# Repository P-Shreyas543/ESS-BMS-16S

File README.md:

# ESS-BMS-16S — Open 16S LFP Battery Management System for Energy Storage

A compact, open-hardware battery management system for 16S LFP (51.2 V) energy-storage packs — home storage, server-rack batteries, telecom backup — designed in KiCad 10 for JLCPCB fabrication and assembly.

The goal is a BMS that matches the features of the widely used Chinese ESS boards (Daly, JBD, JK, Seplos, PACE) and goes beyond them where they are weak: protection that does not depend on firmware, measured switch and pre-charge health, deeper diagnostics, and open, documented protocols.

> **Status (2026-11-25): schematic v1.2 done — PCB layout next. Not built, not tested, not production ready.**
> v1.2 installs a hybrid control-board power tree: restores the v1.0 `+5V` LM5013 non-synchronous buck with the commercial `LM5013DDAR` and v1.0 power latch, and keeps the v1.1 transformer-isolated (2.5 kVAC) `+5V_ISO` chain with the AEC-Q100 `SN6505B-Q1` ([what changed](docs/SCHEMATIC_V1.md#10-revision-v12-2026-11-25)).
> The schematic is complete for both boards of the stack (control board + power board), verified against its pin-level spec and independently reviewed: [`docs/SCHEMATIC_V1.md`](docs/SCHEMATIC_V1.md), PDFs [control board](docs/schematic/control_board_v1.pdf) / [power board](docs/schematic/power_board_v1.pdf). Do not order boards from this repository yet: several bring-up gates (including an LM5013 EMC pre-scan) and owner decisions are open. See [Project status](#project-status).

---

## Target specification (v1)

| Item | Target |
|---|---|
| Cells | 16S LFP, 40.0–58.4 V pack |
| Current | 200 A continuous, on-board back-to-back high-side N-MOSFET switch |
| Current sense | on-board 100 µΩ shunt, BQ76952 coulomb counter + independent fast trip |
| Cell monitor | TI BQ76952 (16 cells, hardware protections, high-side FET drivers, pre-charge) |
| Balancing | external passive ~105 mA per cell + header for an optional 1–2 A active balancer, charge-based balancing firmware |
| Temperature | pack NTCs + FET-bank and shunt sensors |
| MCU | STM32G473RCT6 (3× FDCAN, 256 KB flash) |
| Communications | 2× isolated CAN, 2× isolated RS-485 (inverter + parallel-pack link, RJ45 ×4), ESP32-C3 Bluetooth / Wi-Fi |
| Safety | MCU-independent hardware gate-kill (AFE faults + latched over-current), dual watchdog, switch / pre-charge fault checks |
| Other | sleep / ship mode with wake button, SOC LEDs, 2 dry contacts, heater output, RTC-stamped fault log (FRAM + flash), field firmware update |

The numbers above are design targets; the verified values are kept in [`PROJECT.md`](PROJECT.md) and the architecture documents as they are confirmed.

## How it compares

A feature benchmark of current Daly, JBD, JK, Seplos, PACE and ANT products is in [`docs/research/02_competitors.md`](docs/research/02_competitors.md). In short: every serious product has sleep mode, an app, parallel packs, dry contacts and inverter protocols — this design adds those, plus features none of them documents (independent hardware trip, switch health checks, busbar / cell resistance diagnostics, open protocols, timestamped deep logging).

## Project status

| Step | State |
|---|---|
| Requirements and original runbook | done ([`instructions.md`](instructions.md)) |
| Schematic redraw to house style (6 sheets, connectivity proven unchanged) | done 2026-11-17 |
| Electrical / requirements review | done — findings in [`docs/research/`](docs/research/) and [`AGENT_TASKS.md`](AGENT_TASKS.md) |
| Feature and component research (AFE, competitors, balancing, power path, MCU) | done — [`docs/research/00_SUMMARY.md`](docs/research/00_SUMMARY.md) |
| Architecture v1 (power tree, power stage, AFE, MCU pin map, sheet plan) | done — [`docs/ARCHITECTURE.md`](docs/ARCHITECTURE.md) (updated for schematic v1) |
| Part selection with live LCSC verification | done — [`docs/BOM_v1.md`](docs/BOM_v1.md) |
| Schematic v1 / v1.2: two KiCad projects, 10 sheets, 784 references (v1.2); pin-level spec → independent review → scripted drawing → netlist-vs-spec match on all 10 sheets, ERC 0 errors on both boards → final independent review (0 blockers) + v1-vs-v1.1 comparison | v1 done 2026-11-24, v1.1 2026-11-25 (`ca3a7a3` fallback), v1.2 hybrid power tree 2026-11-25 — [`docs/SCHEMATIC_V1.md`](docs/SCHEMATIC_V1.md), [design notes](docs/design/), [reviews](docs/reviews/), [BOM CSV](docs/bom/bom_schematic_v1.csv) |
| PCB layout, DRC, fabrication outputs | **next** |
| Bring-up and bench tests (incl. the short-circuit test) | planned |

## System block diagram

*Interactive full-resolution diagram: [`docs/block_diagram.svg`](docs/block_diagram.svg) (power path, power board hardware safety island, B2B stack interface, control board v1.2 hybrid power tree, comms, IO, pending owner decisions, and planned additions).*

## Repository layout

| Path | Content |
|---|---|
| `Automotive_ESS_BMS.kicad_pro` / `.kicad_sch` | control-board KiCad project and root schematic (with block diagram) |
| `01_*`, `02_*`, `03_*`, `05_*`, `06_*`, `08_*`, `09_*`, `10_*.kicad_sch` | control-board sheets: power supply, AFE / cell monitor, MCU, aux outputs, communications, IO / front panel, wireless, memory / sensors |
| `power_board/` | power-board KiCad project: `04_Current_Sensing`, `07_Power_Stage` |
| `docs/SCHEMATIC_V1.md`, `docs/schematic/` | schematic v1 overview (board split, B2B pin map, verification, bring-up gates, firmware rules, open decisions) and PDFs of both boards |
| `docs/design/`, `docs/reviews/` | per-sheet design notes (calculations, decisions, LCSC verification) and the spec / schematic reviews |
| `docs/ARCHITECTURE.md`, `docs/architecture/`, `docs/BOM_v1.md`, `docs/bom/` | system architecture and part selection |
| `symbols/`, `footprints.pretty/`, `3d_models/` | project-local libraries (`${KIPRJMOD}` paths, portable) |
| `PROJECT.md` | project facts, nets, domains, parts and the owner **decisions log** |
| `DESIGN_NOTES.md` | calculations and design reasoning, per sheet |
| `docs/research/` | research reports with datasheet / source citations |
| `docs/plans/` | the original 2026-10 subsystem plans (historical background; the decisions log in `PROJECT.md` wins) |
| `LICENSE`, `tools/LICENSE` | CERN-OHL-S-2.0 (hardware), MIT (tools) |
| `instruction.md` | the engineering playbook this project follows (workflow, style, verification) |
| `instructions.md` | original product requirements |
| `AGENT_TASKS.md` | task queue and verification reports of each work step |
| `tools/` | Python helpers: environment check, lossless KiCad s-expression edit, netlist compare, ERC summary, render |

## Engineering method

Every change follows [`instruction.md`](instruction.md):

* **Connectivity proof:** each redraw is verified with a netlist comparison (`tools/schematic/netcmp.py`) — the net list must be identical unless a change was decided.
* **ERC** on the root sheet after every step, with the result recorded.
* **Visual check** of every sheet and block from rendered images.
* **Part data** verified on the distributor page (LCSC number, MPN, stock) — never from memory.
* **Decisions** recorded with date in `PROJECT.md`; calculations in `DESIGN_NOTES.md` with datasheet page references (`DS p.x`), own calculations (`calc`) and estimates (`est.`) marked.

## Opening the project

1. Install KiCad 10.
2. Open `Automotive_ESS_BMS.kicad_pro`. The project libraries resolve through `${KIPRJMOD}`; no global library setup is needed.
3. Optional: `python tools/check_env.py .` checks the toolchain (KiCad CLI, Python packages, renderer).

## Standards referenced

IPC-2221B (clearance), IPC-7351B (land patterns), IPC-A-610 Class 3, IEC 60664-1, IEC 62619 / UL 1973 (stationary storage), UL 9540A, ISO 26262 principles, AEC-Q100/101/200 where available. Certification is not claimed.

## Third-party material

* **Datasheets and app notes are not included.** They are copyrighted by their manufacturers. The design notes and research reports cite them by document number and page; download them from the manufacturer (TI, ST, Vishay, …) or the LCSC product page.
* **3D models are not included** (vendor licences vary). Footprints reference them under `${KIPRJMOD}/3d_models/`; fetch them from the manufacturer or with `easyeda2kicad` for local use.
* Product and company names (Daly, JBD, JK, Seplos, PACE, ANT, Pylontech, Victron, …) are trademarks of their owners and are used only to identify products in the comparison. Competitor data is taken from public documents and listings, cited in `docs/research/02_competitors.md`; no affiliation or endorsement is implied.

## Disclaimer

This is a **work-in-progress design shared for learning and review, not a certified product.** Lithium battery packs store large amounts of energy; a fault in a BMS can cause fire, explosion, electric shock or injury. Anyone who builds, modifies or uses this design does so at their own risk and is responsible for testing it and for meeting the safety standards that apply where it is used (for example IEC 62619, UL 1973, UL 9540A). The design is provided **"as is", without any warranty**, as stated in section 6 (Disclaimer and Liability) of the CERN-OHL-S-2.0 licence. No certification or compliance is claimed.

## License

* **Hardware** (schematics, PCB, libraries, design documentation): [CERN Open Hardware Licence v2 — Strongly Reciprocal](LICENSE) (`CERN-OHL-S-2.0`). You may use, modify, make and sell it; if you distribute a modified design or products made from it, you must publish your modified source under the same licence.
* **Software tools** in `tools/`: [MIT](tools/LICENSE).

Copyright © 2026 Shreyas P. Source location: this repository.

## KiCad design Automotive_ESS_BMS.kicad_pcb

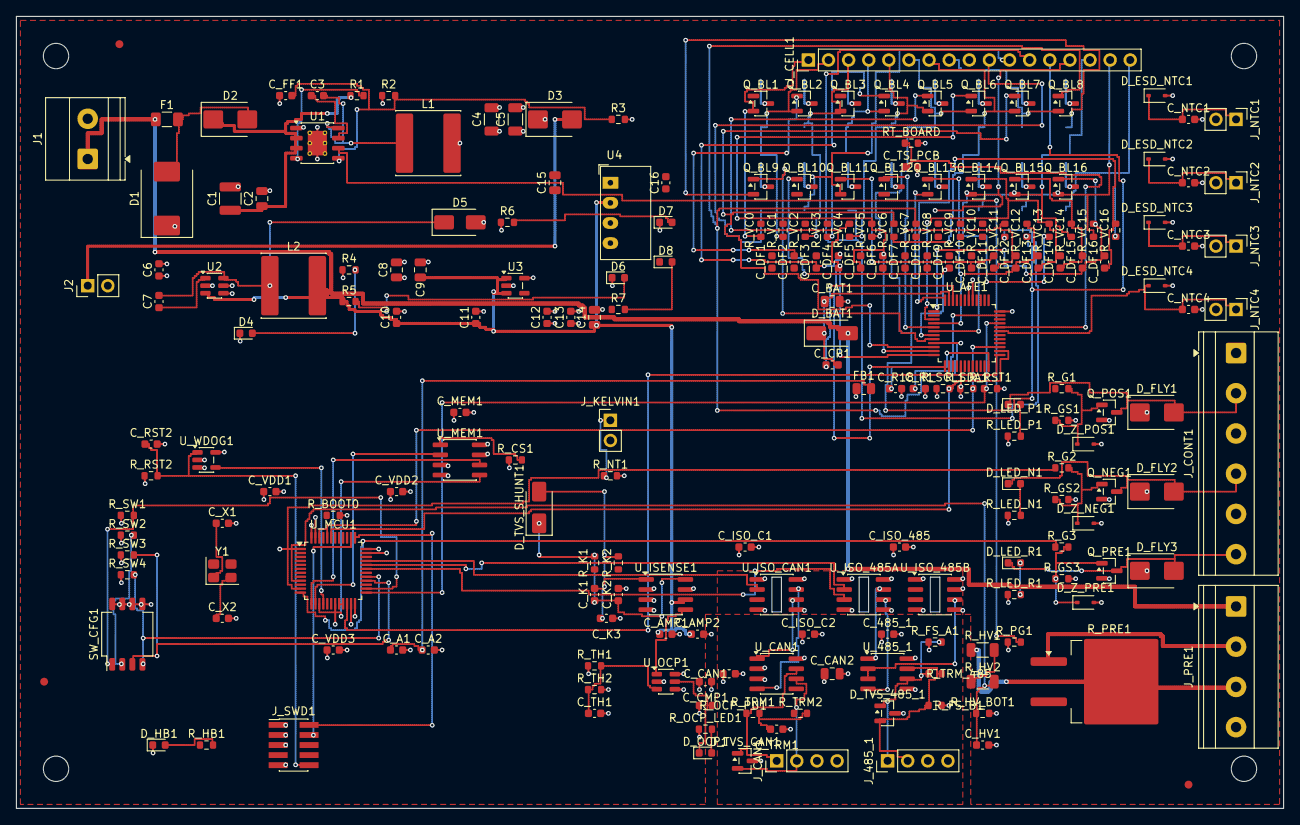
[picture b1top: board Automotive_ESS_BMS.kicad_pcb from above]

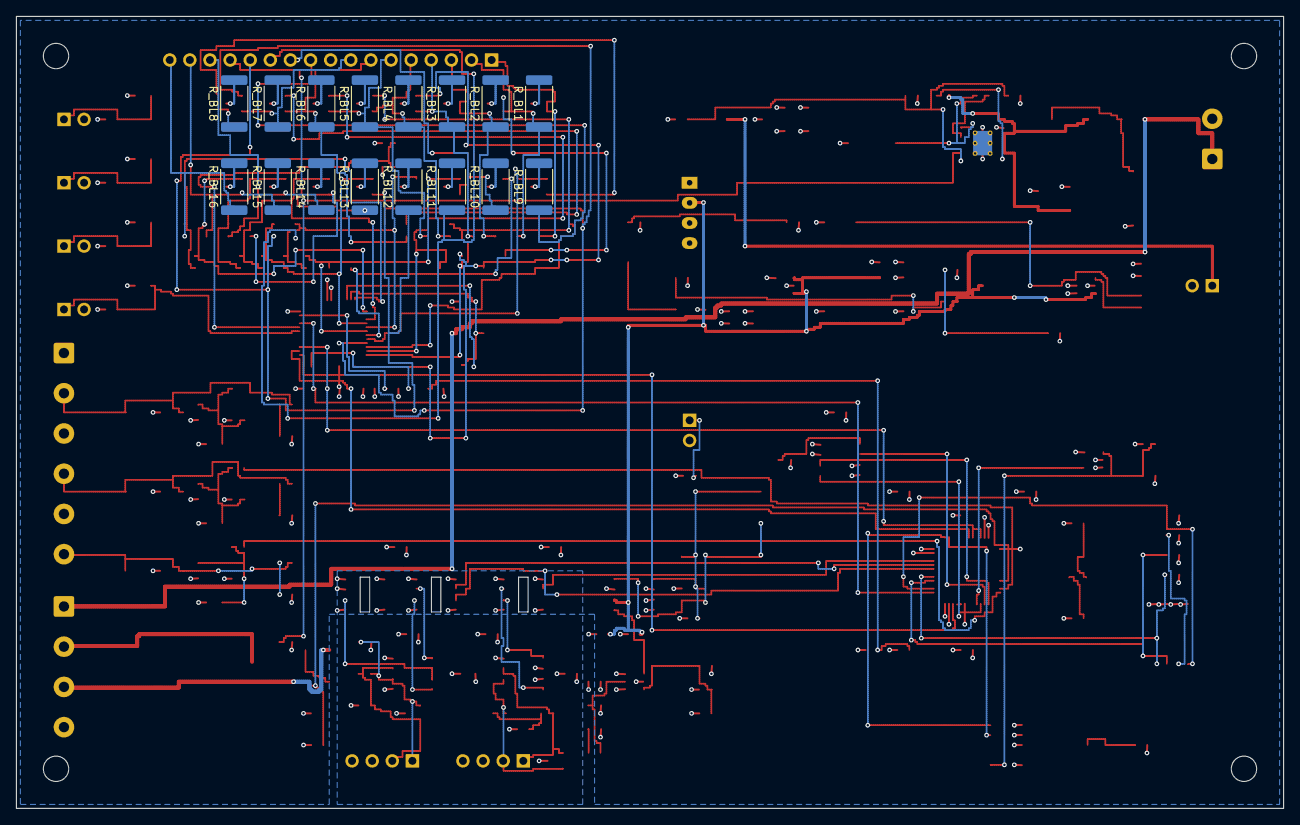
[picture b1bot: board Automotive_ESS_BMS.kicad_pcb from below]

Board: 4 copper layers, 160.0 x 100.0 mm, 231 parts (16 on the bottom side), 141 nets.

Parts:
C1: 10uF 100V; C_1210_3225Metric
C2: 100nF 100V; C_0805_2012Metric
C3, C6, C16: 100nF 50V; C_0603_1608Metric
C4: 22uF 25V; C_1206_3216Metric
C5: 10uF 25V; C_1206_3216Metric
C7: 100nF 25V; C_0603_1608Metric
C8: 10uF 25V; C_0805_2012Metric
C9: 22uF 10V; C_0805_2012Metric
C10, C13: 100nF 16V; C_0603_1608Metric
C11: 1uF 16V; C_0603_1608Metric
C12: 4.7uF 10V; C_0603_1608Metric
C14: 4.7uF 16V; C_0805_2012Metric
C15: 10uF 16V; C_0805_2012Metric
C_485_1: 100nF 16V; C_0603_1608Metric
C_A1: 1uF 16V; C_0603_1608Metric
C_A2: 100nF 16V; C_0603_1608Metric
C_AMP1: 1uF 16V; C_0603_1608Metric
C_AMP2: 100nF 16V; C_0603_1608Metric
C_BAT1: 1uF 100V; C_0805_2012Metric
C_CAN1: 100nF 16V; C_0603_1608Metric
C_CAN2: 4.7uF 16V; C_0805_2012Metric
C_CMP1: 100nF 16V; C_0603_1608Metric
C_CP1: 100nF 50V; C_0603_1608Metric
C_DF1, C_DF2, C_DF3, C_DF4, C_DF5, C_DF6, C_DF7, C_DF8, C_DF9, C_DF10, C_DF11, C_DF12, C_DF13, C_DF14, C_DF15, C_DF16: 100nF 50V; C_0603_1608Metric
C_FF1: 47pF 50V; C_0603_1608Metric
C_HV1: 10nF 50V; C_0603_1608Metric
C_ISO_485: 100nF 16V; C_0603_1608Metric
C_ISO_C1, C_ISO_C2: 100nF 16V; C_0603_1608Metric
C_K1: 100nF 50V; C_0603_1608Metric
C_K2, C_K3: 10nF 50V; C_0603_1608Metric
C_MEM1: 100nF 16V; C_0603_1608Metric
C_NTC1, C_NTC2, C_NTC3, C_NTC4: 10nF 50V; C_0603_1608Metric
C_R1, C_R18: 2.2uF 10V; C_0603_1608Metric
C_RST2: 100nF 16V; C_0603_1608Metric
C_TH1: 10nF 50V; C_0603_1608Metric
C_TRM1: 4.7nF 50V; C_0603_1608Metric
C_TS_PCB: 10nF 50V; C_0603_1608Metric
C_VDD1, C_VDD2, C_VDD3: 100nF 16V; C_0603_1608Metric
C_X1, C_X2: 18pF 50V; C_0603_1608Metric
D1: SMCJ75A; D_SMC
D2: SS310 (100V 3A); D_SMB
D3: SS34 (40V 3A); D_SMB
D4: Blue 12V; LED_0603_1608Metric
D5: SS14; D_SMA
D6: Yellow 5V; LED_0603_1608Metric
D7: Green 3V3; LED_0603_1608Metric
D8: Orange 5V_ISO; LED_0603_1608Metric
D_BAT1: SS110 (100V 1A); D_SMA
D_ESD_NTC1, D_ESD_NTC2, D_ESD_NTC3, D_ESD_NTC4: ESD5V0D3B; D_SOD-323
D_FLY1, D_FLY2, D_FLY3: SS34 (40V 3A); D_SMB
D_HB1: Blue Heartbeat; LED_0603_1608Metric
D_LED_N1: Green Cont- ON; LED_0603_1608Metric
D_LED_P1: Green Cont+ ON; LED_0603_1608Metric
D_LED_R1: Amber Precharge ON; LED_0603_1608Metric
D_OCP1: Red OCP Trip; LED_0603_1608Metric
D_TVS_485_1: SM712; SOT-23
D_TVS_CAN1: NUP2105LT1G; SOT-23
D_TVS_SHUNT1: SMAJ5.0CA; D_SMA
D_Z_NEG1: BZX84-C18 (18V Clamp); D_SOD-323
D_Z_POS1: BZX84-C18 (18V Clamp); D_SOD-323
D_Z_PRE1: BZX84-C18 (18V Clamp); D_SOD-323
F1: 2.5A 125V; Fuse_1206_3216Metric
FB1: 600R @ 100MHz; R_0805_2012Metric
FID1, FID2, FID3: Fiducial_1mm_Mask2mm
J1: Pack Input (16V-72V); TerminalBlock_Phoenix_MKDS-1,5-2-5.08_1x02_P5.08mm_Horizont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
J2: Aux Bench 12V; PinHeader_1x02_P2.54mm_Vertical
J_485_1: Isolated RS-485 Modbus; PinHeader_1x04_P2.54mm_Vertical
J_CAN1: Isolated CAN-FD Bus; PinHeader_1x04_P2.54mm_Vertical
J_CELL1: 16S Cell Sense Tap; PinHeader_1x17_P2.54mm_Vertical
J_CONT1: Contactor Coils (12V); TerminalBlock_Phoenix_MKDS-1,5-6-5.08_1x06_P5.08mm_Horizont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
J_KELVIN1: Ext Shunt Kelvin Sense; PinHeader_1x02_P2.54mm_Vertical
J_NTC1: NTC Temp Sens 1; PinHeader_1x02_P2.54mm_Vertical
J_NTC2: NTC Temp Sens 2; PinHeader_1x02_P2.54mm_Vertical
J_NTC3: NTC Temp Sens 3; PinHeader_1x02_P2.54mm_Vertical
J_NTC4: NTC Temp Sens 4; PinHeader_1x02_P2.54mm_Vertical
J_PRE1: Inverter DC Bus Precharge; TerminalBlock_Phoenix_MKDS-1,5-4-5.08_1x04_P5.08mm_Horizont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
J_SWD1: Cortex SWD Debug; PinHeader_2x05_P1.27mm_Vertical_SMD
L1: 47uH 1.8A; L_Sunlord_SWPA8040S
L2: 10uH 1.5A; L_Sunlord_SWPA8040S
MH1, MH2, MH3, MH4: MountingHole_3.2mm_M3
Q_BL1, Q_BL2, Q_BL3, Q_BL4, Q_BL5, Q_BL6, Q_BL7, Q_BL8, Q_BL9, Q_BL10, Q_BL11, Q_BL12, Q_BL13, Q_BL14, Q_BL15, Q_BL16: AO3400A (30V 5A); SOT-23
Q_NEG1: SQ2318EY (40V 8A); SOT-23
Q_POS1: SQ2318EY (40V 8A); SOT-23
Q_PRE1: SQ2318EY (40V 8A); SOT-23
R1: 100k; R_0603_1608Metric
R2: 90.9k 1%; R_0603_1608Metric
R3: 10.0k 1%; R_0603_1608Metric
R4: 4.7k; R_0603_1608Metric
R5, R7: 1.5k; R_0603_1608Metric
R6: 1.0k; R_0603_1608Metric
RT_BOARD: NTC 10k 1% (PCB Temp); R_0603_1608Metric
R_BL1, R_BL2, R_BL3, R_BL4, R_BL5, R_BL6, R_BL7, R_BL8, R_BL9, R_BL10, R_BL11, R_BL12, R_BL13, R_BL14, R_BL15, R_BL16: 33R 1W 1%; R_2512_6332Metric
R_BOOT0: 10k; R_0603_1608Metric
R_CS1: 10k; R_0603_1608Metric
R_FS_A1: 560R 1%; R_0603_1608Metric
R_FS_B1: 560R 1%; R_0603_1608Metric
R_G1, R_G2, R_G3: 100R; R_0603_1608Metric
R_GS1, R_GS2, R_GS3: 47k; R_0603_1608Metric
R_HB1: 1.0k; R_0603_1608Metric
R_HV1, R_HV2: 1.00M 1% 200V; R_1206_3216Metric
R_HV_BOT1: 20.0k 0.1%; R_0603_1608Metric
R_K1, R_K2: 10.0R 1%; R_0603_1608Metric
R_LED_N1: 4.7k; R_0603_1608Metric
R_LED_P1: 4.7k; R_0603_1608Metric
R_LED_R1: 4.7k; R_0603_1608Metric
R_NT1: 0R (Kelvin Ground Tie); R_0603_1608Metric
R_OCP_LED1: 1.5k; R_0603_1608Metric
R_OCP_PU1: 10k; R_0603_1608Metric
R_PG1: 100k; R_0603_1608Metric
R_PRE1: 50R 25W 5%; TO-263-2
R_RST1, R_RST2: 10k; R_0603_1608Metric
R_SCL1: 4.7k; R_0603_1608Metric
R_SDA1: 4.7k; R_0603_1608Metric
R_SW1, R_SW2, R_SW3, R_SW4: 10k; R_0603_1608Metric
R_TH1: 4.7k 1%; R_0603_1608Metric
R_TH2: 100k 1%; R_0603_1608Metric
R_TRM1, R_TRM2: 60.4R 1%; R_0603_1608Metric
R_TRM_485: 120R 1%; R_0603_1608Metric
R_VC0, R_VC1, R_VC2, R_VC3, R_VC4, R_VC5, R_VC6, R_VC7, R_VC8, R_VC9, R_VC10, R_VC11, R_VC12, R_VC13, R_VC14, R_VC15, R_VC16: 1.00k 1%; R_0603_1608Metric
SW_CFG1: 7S-16S & Chem CFG; SW_DIP_SPSTx04_Slide_Copal_CHS-04B_W7.62mm_P1.27mm
U1: LM5164-Q1; HSOP-8-1EP_3.9x4.9mm_P1.27mm_EP2.41x3.1mm_ThermalVias
U2: LMR16006YQ5; SOT-23-6
U3: AP2112K-3.3; SOT-23-5
U4: B0505S-1WR3; Converter_DCDC_Murata_CRE1xxxxxxSC_THT
U_485_1: THVD1450DR; SOIC-8_3.9x4.9mm_P1.27mm
U_AFE1: BQ76952-Q1; TQFP-48_7x7mm_P0.5mm
U_CAN1: TJA1051T/3; SOIC-8_3.9x4.9mm_P1.27mm
U_ISENSE1: INA240A2-Q1; SOIC-8_3.9x4.9mm_P1.27mm
U_ISO_485A, U_ISO_485B: ISO7721-Q1; SOIC-8_3.9x4.9mm_P1.27mm
U_ISO_CAN1: ISO7721-Q1; SOIC-8_3.9x4.9mm_P1.27mm
U_MCU1: STM32G431CBT6; LQFP-48_7x7mm_P0.5mm
U_MEM1: 25LC256-I/SN; SOIC-8_3.9x4.9mm_P1.27mm
U_OCP1: TLV3501AIDBVR; SOT-23-6
U_WDOG1: TPS3823-33DBVR; SOT-23-5
Y1: 8.000MHz; Crystal_SMD_3225-4Pin_3.2x2.5mm

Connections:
+3V3: C12.1, C13.1, C_CMP1.1, C_ISO_485.1, C_ISO_C1.1, C_MEM1.1, C_VDD1.1, C_VDD2.1, C_VDD3.1, FB1.1, J_SWD1.1, R6.1, R_CS1.1, R_OCP_LED1.1, R_OCP_PU1.1, R_RST2.1, R_SCL1.1, R_SDA1.1, R_SW1.1, R_SW2.1, R_SW3.1, R_SW4.1, R_TH1.1, U3.5, U_ISENSE1.7, U_ISO_485A.1, U_ISO_485B.1, U_ISO_CAN1.1, U_MCU1.1, U_MCU1.24, U_MCU1.36, U_MCU1.48, U_MEM1.3, U_MEM1.7, U_MEM1.8, U_OCP1.4, U_OCP1.6, U_WDOG1.3, U_WDOG1.5
+3V3_A: C_A1.1, C_A2.1, FB1.2, U_MCU1.20, U_MCU1.21
+5V: C9.1, C10.1, C11.1, C14.1, C_AMP1.1, C_AMP2.1, L2.2, R5.1, U2.3, U3.1, U3.3, U4.2, U_ISENSE1.6
+5V_ISO: C15.1, C16.1, C_485_1.1, C_CAN1.1, C_CAN2.1, C_ISO_C2.1, J_485_1.4, J_CAN1.4, R7.1, R_FS_A1.1, U4.4, U_485_1.8, U_CAN1.3, U_ISO_485A.8, U_ISO_485B.8, U_ISO_CAN1.8
+12V: C4.1, C5.1, C6.1, C8.1, C_FF1.1, D3.1, D_FLY1.1, D_FLY2.1, D_FLY3.1, J_CONT1.1, J_CONT1.3, J_CONT1.5, L1.2, R2.1, R4.1, R_LED_N1.1, R_LED_P1.1, R_LED_R1.1, R_PG1.1, U2.4, U2.5
ADC_I_SENSE: U_ISENSE1.5, U_MCU1.8, U_OCP1.1
AFE_ALERT: U_AFE1.25, U_MCU1.22
AFE_RST: R_RST1.1, U_AFE1.33, U_MCU1.25
AFE_SCL: R_SCL1.2, U_AFE1.26, U_MCU1.43
AFE_SDA: R_SDA1.2, U_AFE1.27, U_MCU1.44, U_MCU1.46
AMP_IN+: C_K1.1, C_K2.1, D_TVS_SHUNT1.1, R_K1.2, U_ISENSE1.8
AMP_IN-: C_K1.2, C_K3.1, D_TVS_SHUNT1.2, R_K2.2, U_ISENSE1.1
CAN_RX: U_ISO_CAN1.2, U_MCU1.33
CAN_RX_ISO: U_CAN1.4, U_ISO_CAN1.7
CAN_TX: U_ISO_CAN1.3, U_MCU1.34
CAN_TX_ISO: U_CAN1.1, U_ISO_CAN1.6
CELL_0: J_CELL1.1, Q_BL1.2, R_VC0.1
CELL_1: J_CELL1.2, Q_BL2.2, R_BL1.1, R_VC1.1
CELL_2: J_CELL1.3, Q_BL3.2, R_BL2.1, R_VC2.1
CELL_3: J_CELL1.4, Q_BL4.2, R_BL3.1, R_VC3.1
CELL_4: J_CELL1.5, Q_BL5.2, R_BL4.1, R_VC4.1
CELL_5: J_CELL1.6, Q_BL6.2, R_BL5.1, R_VC5.1
CELL_6: J_CELL1.7, Q_BL7.2, R_BL6.1, R_VC6.1
CELL_7: J_CELL1.8, Q_BL8.2, R_BL7.1, R_VC7.1
CELL_8: J_CELL1.9, Q_BL9.2, R_BL8.1, R_VC8.1
CELL_9: J_CELL1.10, Q_BL10.2, R_BL9.1, R_VC9.1
CELL_10: J_CELL1.11, Q_BL11.2, R_BL10.1, R_VC10.1
CELL_11: J_CELL1.12, Q_BL12.2, R_BL11.1, R_VC11.1
CELL_12: J_CELL1.13, Q_BL13.2, R_BL12.1, R_VC12.1
CELL_13: J_CELL1.14, Q_BL14.2, R_BL13.1, R_VC13.1
CELL_14: J_CELL1.15, Q_BL15.2, R_BL14.1, R_VC14.1
CELL_15: J_CELL1.16, Q_BL16.2, R_BL15.1, R_VC15.1
CELL_16: J_CELL1.17, R_BL16.1, R_VC16.1
CFG_CELL_0: R_SW2.2, SW_CFG1.2, U_MCU1.27
CFG_CELL_1: R_SW3.2, SW_CFG1.3, U_MCU1.28
CFG_CELL_2: R_SW4.2, SW_CFG1.4, U_MCU1.29
CFG_CHEM: R_SW1.2, SW_CFG1.1, U_MCU1.26
COIL_NEG-: D_FLY2.2, D_LED_N1.1, J_CONT1.4, Q_NEG1.3
COIL_POS-: D_FLY1.2, D_LED_P1.1, J_CONT1.2, Q_POS1.3
COIL_PRE-: D_FLY3.2, D_LED_R1.1, J_CONT1.6, Q_PRE1.3
CTRL_CONT_NEG: R_G2.1, U_MCU1.11
CTRL_CONT_POS: R_G1.1, U_MCU1.10
CTRL_PRECHARGE: R_G3.1, U_MCU1.12
GND_ISO: C15.2, C16.2, C_485_1.2, C_CAN1.2, C_CAN2.2, C_ISO_C2.2, C_TRM1.2, D8.1, D_TVS_485_1.3, D_TVS_CAN1.3, J_485_1.3, J_CAN1.3, R_FS_B1.2, U4.3, U_485_1.5, U_CAN1.2, U_CAN1.8, U_ISO_485A.5, U_ISO_485B.5, U_ISO_485B.7, U_ISO_CAN1.5
GND_PWR: C1.2, C2.2, C4.2, C5.2, C6.2, C8.2, C9.2, C10.2, C11.2, C12.2, C13.2, C14.2, C_A1.2, C_A2.2, C_AMP1.2, C_AMP2.2, C_BAT1.2, C_CMP1.2, C_HV1.2, C_ISO_485.2, C_ISO_C1.2, C_K2.2, C_K3.2, C_MEM1.2, C_NTC1.2, C_NTC2.2, C_NTC3.2, C_NTC4.2, C_R1.2, C_R18.2, C_RST2.2, C_TH1.2, C_TS_PCB.2, C_VDD1.2, C_VDD2.2, C_VDD3.2, C_X1.2, C_X2.2, D1.1, D4.1, D5.2, D6.1, D7.1, D_ESD_NTC1.2, D_ESD_NTC2.2, D_ESD_NTC3.2, D_ESD_NTC4.2, D_HB1.1, D_Z_NEG1.2, D_Z_POS1.2, D_Z_PRE1.2, J1.2, J2.2, J_NTC1.2, J_NTC2.2, J_NTC3.2, J_NTC4.2, J_PRE1.4, J_SWD1.3, J_SWD1.5, J_SWD1.9, Q_NEG1.2, Q_POS1.2, Q_PRE1.2, R3.2, RT_BOARD.2, R_BOOT0.2, R_GS1.2, R_GS2.2, R_GS3.2, R_HV_BOT1.2, R_NT1.2, R_RST1.2, R_TH2.2, SW_CFG1.5, SW_CFG1.6, SW_CFG1.7, SW_CFG1.8, U1.1, U1.9, U2.2, U3.2, U4.1, U_AFE1.17, U_AFE1.36, U_AFE1.41, U_AFE1.42, U_ISENSE1.2, U_ISENSE1.3, U_ISENSE1.4, U_ISO_485A.4, U_ISO_485B.4, U_ISO_CAN1.4, U_MCU1.19, U_MCU1.23, U_MCU1.35, U_MCU1.47, U_MEM1.4, U_OCP1.2, U_WDOG1.2
MCU_BOOT0: R_BOOT0.1, U_MCU1.45
MCU_HEARTBEAT: R_HB1.1, U_MCU1.2
MCU_RESET_N: C_RST2.1, J_SWD1.10, R_RST2.2, U_MCU1.7, U_WDOG1.1
MCU_WDOG_WDI: U_MCU1.16, U_WDOG1.4
NET_BAL1: Q_BL1.3, R_BL1.2
NET_BAL2: Q_BL2.3, R_BL2.2
NET_BAL3: Q_BL3.3, R_BL3.2
NET_BAL4: Q_BL4.3, R_BL4.2
NET_BAL5: Q_BL5.3, R_BL5.2
NET_BAL6: Q_BL6.3, R_BL6.2
NET_BAL7: Q_BL7.3, R_BL7.2
NET_BAL8: Q_BL8.3, R_BL8.2
NET_BAL9: Q_BL9.3, R_BL9.2
NET_BAL10: Q_BL10.3, R_BL10.2
NET_BAL11: Q_BL11.3, R_BL11.2
NET_BAL12: Q_BL12.3, R_BL12.2
NET_BAL13: Q_BL13.3, R_BL13.2
NET_BAL14: Q_BL14.3, R_BL14.2
NET_BAL15: Q_BL15.3, R_BL15.2
NET_BAL16: Q_BL16.3, R_BL16.2
NET_CANH: D_TVS_CAN1.1, J_CAN1.1, R_TRM1.1, U_CAN1.7
NET_CANL: D_TVS_CAN1.2, J_CAN1.2, R_TRM2.1, U_CAN1.6
NET_CAN_SPLIT: C_TRM1.1, R_TRM1.2, R_TRM2.2
NET_CP1: C_CP1.1, U_AFE1.46
NET_FUSE: D1.2, D2.2, F1.2
NET_GATE_NEG: D_Z_NEG1.1, Q_NEG1.1, R_G2.2, R_GS2.1
NET_GATE_POS: D_Z_POS1.1, Q_POS1.1, R_G1.2, R_GS1.1
NET_GATE_PRE: D_Z_PRE1.1, Q_PRE1.1, R_G3.2, R_GS3.1
NET_HV_MID: R_HV1.2, R_HV2.1
NET_LEDNEG: D_LED_N1.2, R_LED_N1.2
NET_LEDPOS: D_LED_P1.2, R_LED_P1.2
NET_LEDPRE: D_LED_R1.2, R_LED_R1.2
NET_LED_3V3: D7.2, R6.2
NET_LED_5V: D6.2, R5.2
NET_LED_5V_ISO: D8.2, R7.2
NET_LED_12V: D4.2, R4.2
NET_LED_HB: D_HB1.2, R_HB1.2
NET_LED_OCP: D_OCP1.2, R_OCP_LED1.2
NET_LMR_CB: C7.1, U2.1
NET_LMR_SW: C7.2, D5.1, L2.1, U2.6
NET_LM_BOOT: C3.1, U1.7
NET_LM_FB: C_FF1.2, R2.2, R3.1, U1.5
NET_LM_RON: R1.2, U1.4
NET_LM_SW: C3.2, L1.1, U1.8
NET_PRE_IN: J_PRE1.2, R_PRE1.1
NET_REG1: C_R1.1, U_AFE1.35
NET_REG18: C_R18.1, U_AFE1.24
NTC_TS1: C_NTC1.1, D_ESD_NTC1.1, J_NTC1.1, U_AFE1.21
NTC_TS2: C_NTC2.1, D_ESD_NTC2.1, J_NTC2.1, U_AFE1.22
NTC_TS3: C_NTC3.1, D_ESD_NTC3.1, J_NTC3.1, U_AFE1.23
NTC_TS4: C_NTC4.1, D_ESD_NTC4.1, J_NTC4.1, U_AFE1.31
NTC_TS_PCB: C_TS_PCB.1, RT_BOARD.1, U_AFE1.32
OCP_TRIP_N: D_OCP1.1, R_OCP_PU1.2, U_MCU1.30, U_OCP1.5
OSC_IN: C_X1.1, U_MCU1.5, Y1.1
OSC_OUT: C_X2.1, U_MCU1.6, Y1.2
PWR_PGOOD: R_PG1.2, U1.6
RS485_A: D_TVS_485_1.1, J_485_1.1, R_FS_A1.2, R_TRM_485.1, U_485_1.6
RS485_B: D_TVS_485_1.2, J_485_1.2, R_FS_B1.1, R_TRM_485.2, U_485_1.7
RS485_DIR: U_ISO_485B.3, U_MCU1.18
RS485_DIR_ISO: U_485_1.2, U_485_1.3, U_ISO_485B.6
RS485_RX: U_ISO_485A.2, U_MCU1.32
RS485_RX_ISO: U_485_1.1, U_ISO_485A.7
RS485_TX: U_ISO_485A.3, U_MCU1.31
RS485_TX_ISO: U_485_1.4, U_ISO_485A.6
SH_N: J_KELVIN1.2, R_K2.1, U_AFE1.20
SH_P: J_KELVIN1.1, R_K1.1, R_NT1.1, U_AFE1.18
SPI1_CS_MEM: R_CS1.2, U_MCU1.17, U_MEM1.1
SPI1_MISO: U_MCU1.14, U_MEM1.2
SPI1_MOSI: U_MCU1.15, U_MEM1.5
SPI1_SCK: U_MCU1.13, U_MEM1.6
SWCLK: J_SWD1.4, U_MCU1.38
SWDIO: J_SWD1.2, U_MCU1.37
VC0: C_DF1.2, Q_BL1.1, R_VC0.2, U_AFE1.16
VC1: C_DF1.1, C_DF2.2, Q_BL2.1, R_VC1.2, U_AFE1.15
VC2: C_DF2.1, C_DF3.2, Q_BL3.1, R_VC2.2, U_AFE1.14
VC3: C_DF3.1, C_DF4.2, Q_BL4.1, R_VC3.2, U_AFE1.13
VC4: C_DF4.1, C_DF5.2, Q_BL5.1, R_VC4.2, U_AFE1.12
VC5: C_DF5.1, C_DF6.2, Q_BL6.1, R_VC5.2, U_AFE1.11
VC6: C_DF6.1, C_DF7.2, Q_BL7.1, R_VC6.2, U_AFE1.10
VC7: C_DF7.1, C_DF8.2, Q_BL8.1, R_VC7.2, U_AFE1.9
VC8: C_DF8.1, C_DF9.2, Q_BL9.1, R_VC8.2, U_AFE1.8
VC9: C_DF9.1, C_DF10.2, Q_BL10.1, R_VC9.2, U_AFE1.7
VC10: C_DF10.1, C_DF11.2, Q_BL11.1, R_VC10.2, U_AFE1.6
VC11: C_DF11.1, C_DF12.2, Q_BL12.1, R_VC11.2, U_AFE1.5
VC12: C_DF12.1, C_DF13.2, Q_BL13.1, R_VC12.2, U_AFE1.4
VC13: C_DF13.1, C_DF14.2, Q_BL14.1, R_VC13.2, U_AFE1.3
VC14: C_DF14.1, C_DF15.2, Q_BL15.1, R_VC14.2, U_AFE1.2
VC15: C_DF15.1, C_DF16.2, Q_BL16.1, R_VC15.2, U_AFE1.1
VC16: C_DF16.1, R_VC16.2, U_AFE1.48
V_AUX_12V: D3.2, J2.1
V_BATT+: D_BAT1.2, F1.1, J1.1, J_PRE1.1
V_BAT_FILT: C_BAT1.1, C_CP1.2, D_BAT1.1, U_AFE1.47
V_HV_SENSE: C_HV1.1, R_HV2.2, R_HV_BOT1.1, U_MCU1.9
V_INVERTER_BUS: J_PRE1.3, R_HV1.1, R_PRE1.2
V_IN_BUCK: C1.1, C2.1, D2.1, R1.1, U1.2, U1.3
V_TH_OCP: C_TH1.1, R_TH1.2, R_TH2.1, U_OCP1.3
